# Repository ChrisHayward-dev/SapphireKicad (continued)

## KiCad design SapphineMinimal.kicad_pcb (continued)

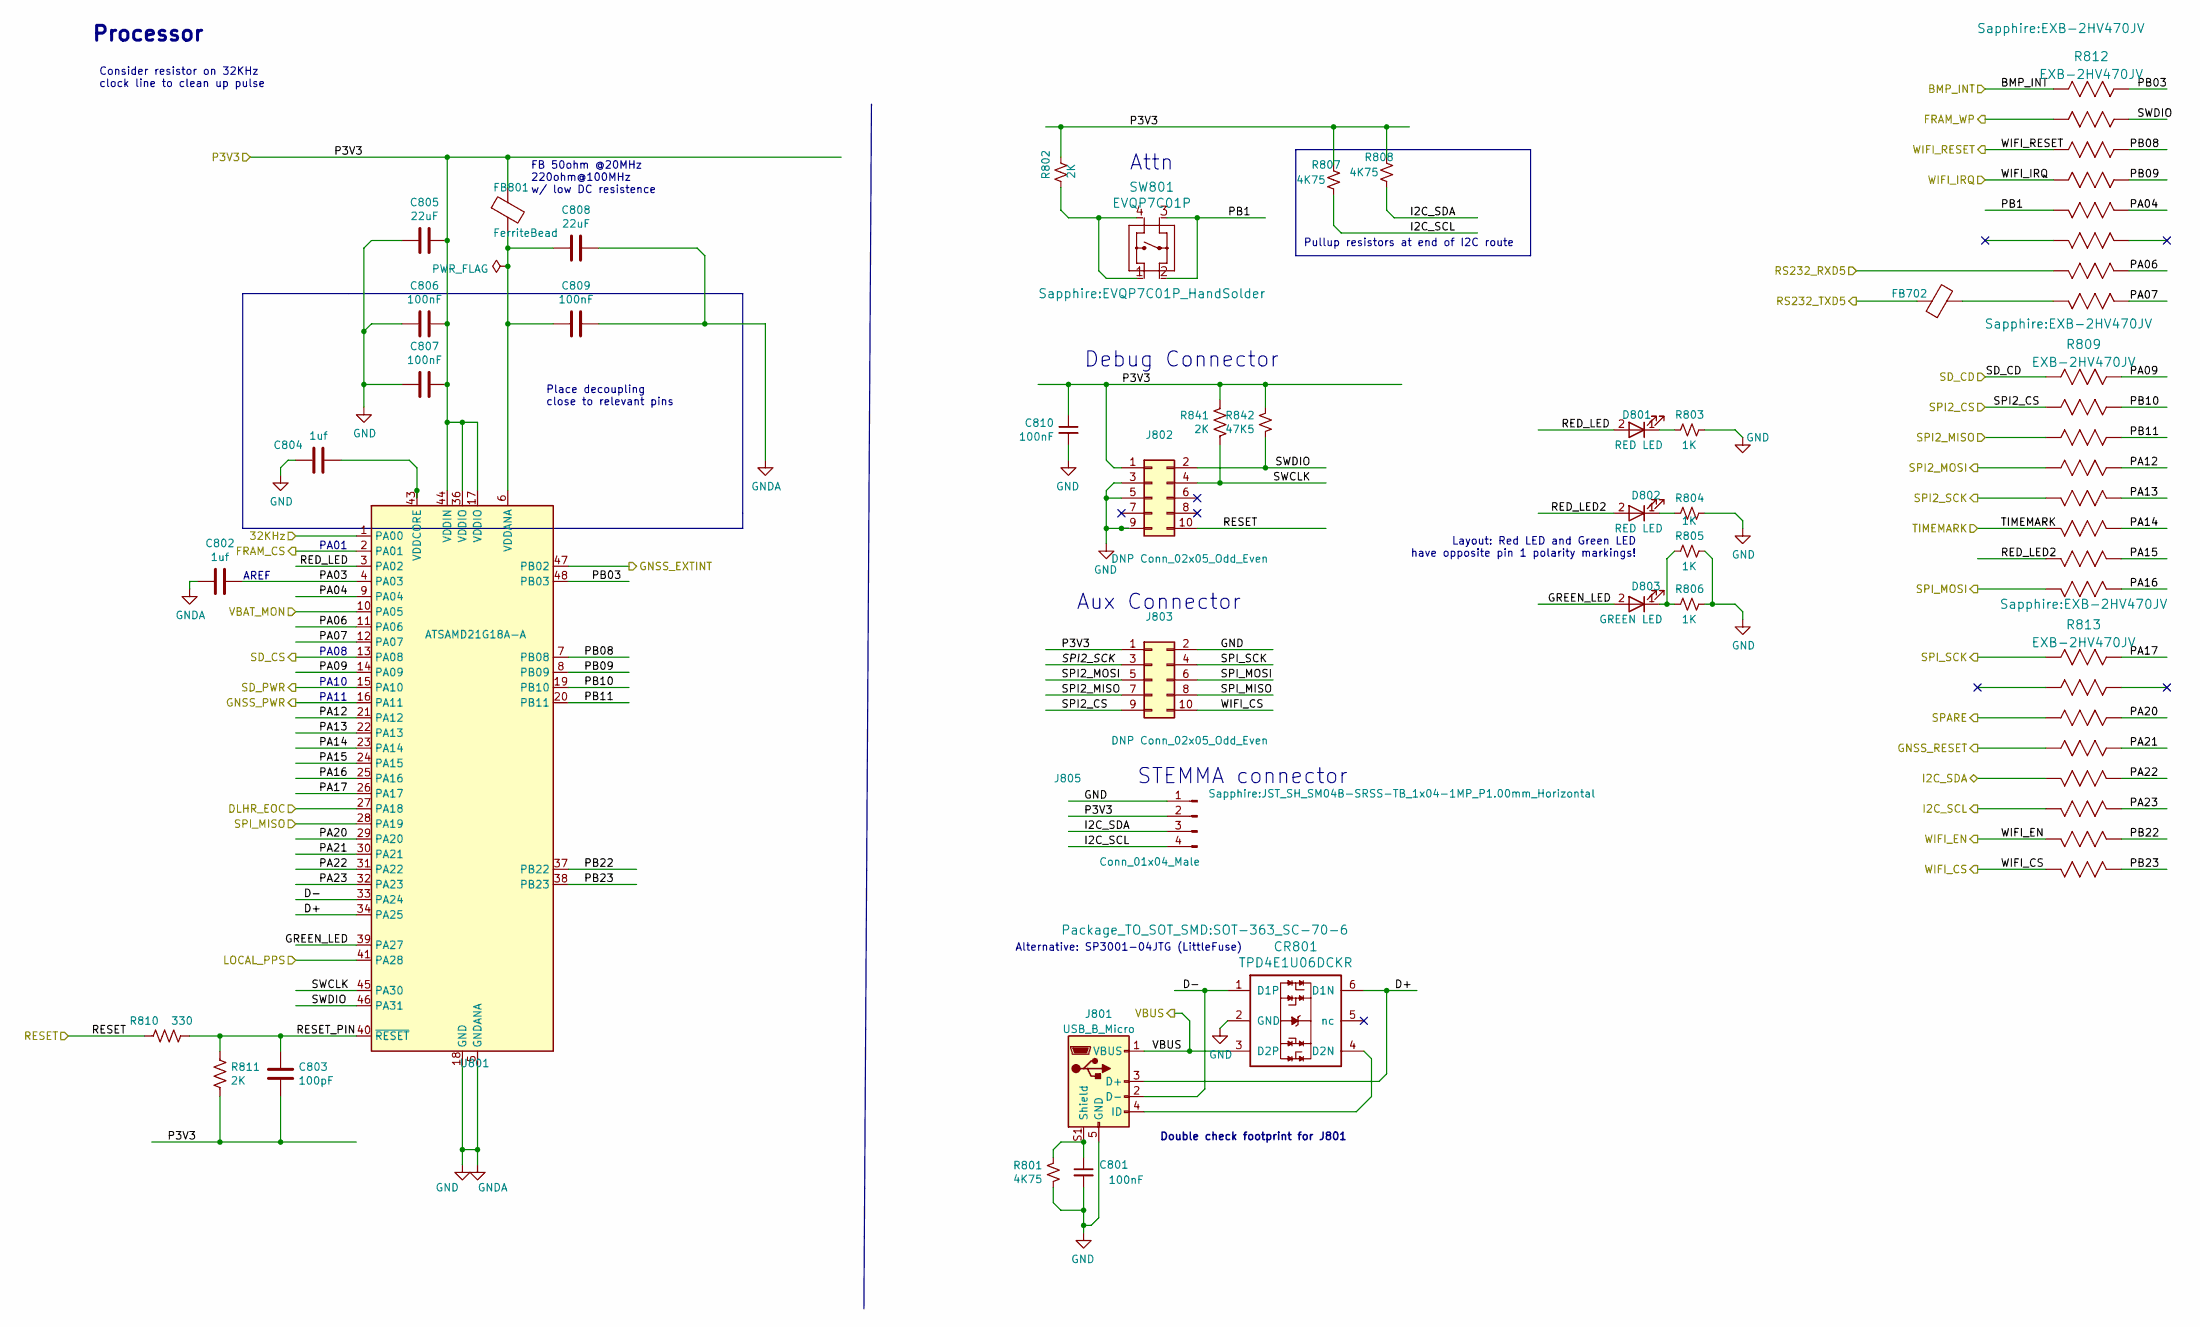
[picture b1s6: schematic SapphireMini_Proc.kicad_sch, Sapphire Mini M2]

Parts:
C801, C810: 100nF; C_0402_1005Metric; Tolerance 10%; Voltage 25; MPN CL05A104KA5NNNC; DigiKey Price 0.10
C802, C804: 1uf; C_0603_1608Metric; Voltage 16; MPN CL21B105KOFNNNG
C803: 100pF; C_0603_1608Metric; MPN 06035A101JAT2A
C805, C808: 22uF; C_0805_2012Metric; Voltage 16; MPN CL21A226MAYNNNE
C806, C807, C809: 100nF; C_0402_1005Metric; Voltage 25; MPN CL05A104KA5NNNC
CR801: TPD4E1U06DCKR; SOT-363_SC-70-6; MPN SP3001-04JTG; Digi-Key_PN F2915CT-ND
D801, D802: RED LED; LED_0805_2012Metric; MPN LTST-S220KRKT; DigiKey Price 0.28
D803: GREEN LED; LED_0805_2012Metric; MPN LTST-S220KGKT; DigiKey Price 0.28
FB702, FB801: FerriteBead; L_0603_1608Metric; MPN BLM18AG221SN1D
J801: USB_B_Micro; FCI_10118193-0001LF; MPN 10118193-0001LF
J802, J803: DNP Conn_02x05_Odd_Even; 3220-10-0100-00; MPN 3220-10-0100-00; DigiKey Price 0.58
J805: Conn_01x04_Male; JST_SH_SM04B-SRSS-TB_1x04-1MP_P1.00mm_Horizontal; MPN SM04B-SRSS-TB(LF)(SN); Digi-Key_PN 455-1804-1-ND
R801, R807, R808: 4K75; R_0603_1608Metric; Tolerance 5%; MPN CRCW06034K75FKEAC; DigiKey Price 0.05
R802: 2K; R_0603_1608Metric; Tolerance 5%; MPN CRCW06032K00FKEAC; DigiKey Price 0.05
R803, R804, R805, R806: 1K; R_0603_1608Metric; Tolerance 5%; MPN CRCW06031K00FKEAC; DigiKey Price 0.05
R809, R812, R813: EXB-2HV470JV; MPN EXB-2HV470JV
R810: 330; R_0603_1608Metric; MPN RC0603JR-07330RL
R811, R841: 2K; R_0603_1608Metric; MPN CRCW06032K00FKEAC
R842: 47K5; R_0603_1608Metric; Tolerance 1%; MPN CRCW060347K5FKEAC; DigiKey Price 0.10
SW801: EVQP7C01P; EVQP7C01P_HandSolder; MPN EVQ-P7C01P; Digi-Key_PN P16765CT-ND
U801: ATSAMD21G18A-A; TQFP-48_7x7mm_P0.5mm; MPN ATSAMD21G18A-AUT

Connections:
/DS3231/32KHz: U801.1 (PA00); also elsewhere on the board
/DS3231/SQW: U801.41 (PA28); also elsewhere on the board
/I2C_SCL: J805.4, R807.2, R813.6; also elsewhere on the board
/I2C_SDA: J805.3, R808.2, R813.5; also elsewhere on the board
/P3V3: C803.1, C805.1, C806.1, C807.1, C810.1, FB801.1, J802.1, J803.1, J805.2, R802.1, R807.1, R808.1, R811.2, R841.1, R842.2, U801.17 (VDDIO), U801.36 (VDDIO), U801.44 (VDDIN); also elsewhere on the board
/SPARE: R813.3; also elsewhere on the board
/SPI2_MISO: J803.7, R809.3; also elsewhere on the board
/SPI2_MOSI: J803.5, R809.4; also elsewhere on the board
/SPI2_SCK: J803.3, R809.5; also elsewhere on the board
/SapphireMini_DLHR/BMP_INT: R812.1; also elsewhere on the board
/SapphireMini_DLHR/DLHR_EOC: U801.27 (PA18); also elsewhere on the board
/SapphireMini_GNSS/GNSS_EXTINT: U801.47 (PB02); also elsewhere on the board
/SapphireMini_GNSS/GNSS_RESET: R813.4; also elsewhere on the board
/SapphireMini_GNSS/RS232_RXD: FB702.1; also elsewhere on the board
/SapphireMini_GNSS/RS232_TXD: R812.7; also elsewhere on the board
/SapphireMini_Power/GNSS_PWR: U801.16 (PA11); also elsewhere on the board
/SapphireMini_Power/SD_PWR: U801.15 (PA10); also elsewhere on the board
/SapphireMini_Power/VBAT_MON: U801.10 (PA05); also elsewhere on the board
/SapphireMini_Power/VBUS: CR801.3 (D2P), J801.1 (VBUS); also elsewhere on the board
/SapphireMini_SD/FRAM_CS: U801.2 (PA01); also elsewhere on the board
/SapphireMini_SD/FRAM_WP: R812.2; also elsewhere on the board
/SapphireMini_SD/SD_CS: U801.13 (PA08); also elsewhere on the board
/SapphireMini_SD/SPI_MISO: J803.8, U801.28 (PA19); also elsewhere on the board
/SapphireMini_SD/SPI_MOSI: J803.6, R809.8; also elsewhere on the board
/SapphireMini_SD/SPI_SCK: J803.4, R813.1; also elsewhere on the board
/Sapphire_Proc/D+: CR801.6 (D1N), J801.3 (D+), U801.34 (PA25)
/Sapphire_Proc/D-: CR801.1 (D1P), J801.2 (D-), U801.33 (PA24)
/Sapphire_Proc/GREEN_LED: D803.2 (A), U801.39 (PA27)
/Sapphire_Proc/PA03: C802.1, U801.4 (PA03)
/Sapphire_Proc/PA04: R812.12, U801.9 (PA04)
/Sapphire_Proc/PA06: R812.10, U801.11 (PA06)
/Sapphire_Proc/PA07: R812.9, U801.12 (PA07)
/Sapphire_Proc/PA09: R809.16, U801.14 (PA09)
/Sapphire_Proc/PA12: R809.13, U801.21 (PA12)
/Sapphire_Proc/PA13: R809.12, U801.22 (PA13)
/Sapphire_Proc/PA14: R809.11, U801.23 (PA14)
/Sapphire_Proc/PA15: R809.10, U801.24 (PA15)
/Sapphire_Proc/PA16: R809.9, U801.25 (PA16)
/Sapphire_Proc/PA17: R813.16, U801.26 (PA17)
/Sapphire_Proc/PA20: R813.14, U801.29 (PA20)
/Sapphire_Proc/PA21: R813.13, U801.30 (PA21)
/Sapphire_Proc/PA22: R813.12, U801.31 (PA22)
/Sapphire_Proc/PA23: R813.11, U801.32 (PA23)
/Sapphire_Proc/PB1: R812.5, SW801.2, SW801.3
/Sapphire_Proc/PB03: R812.16, U801.48 (PB03)
/Sapphire_Proc/PB08: R812.14, U801.7 (PB08)
/Sapphire_Proc/PB09: R812.13, U801.8 (PB09)
/Sapphire_Proc/PB10: R809.15, U801.19 (PB10)
/Sapphire_Proc/PB11: R809.14, U801.20 (PB11)
/Sapphire_Proc/PB22: R813.10, U801.37 (PB22)
/Sapphire_Proc/PB23: R813.9, U801.38 (PB23)
/Sapphire_Proc/RED_LED: D801.2 (A), U801.3 (PA02)
/Sapphire_Proc/RED_LED2: D802.2 (A), R809.7
/Sapphire_Proc/RESET: J802.10, R810.2; also elsewhere on the board
/Sapphire_Proc/RESET_PIN: C803.2, R810.1, R811.1, U801.40 (~RESET)
/Sapphire_Proc/SD_CD: R809.1; also elsewhere on the board
/Sapphire_Proc/SPI2_CS: J803.9, R809.2
/Sapphire_Proc/SWCLK: J802.4, R841.2, U801.45 (PA30)
/Sapphire_Proc/SWDIO: J802.2, R812.15, R842.1, U801.46 (PA31)
/Sapphire_Proc/TIMEMARK: R809.6; also elsewhere on the board
/Sapphire_Proc/WIFI_CS: J803.10, R813.8; also elsewhere on the board
/Sapphire_Proc/WIFI_EN: R813.7; also elsewhere on the board
/WIFI_IRQ: R812.4; also elsewhere on the board
/WIFI_RST: R812.3; also elsewhere on the board
GND: C801.2, C802.2, C804.2, C805.2, C806.2, C807.2, C808.1, C809.1, C810.2, CR801.2 (GND), J801.5 (GND), J802.3, J802.5, J802.9, J803.2, J805.1, R801.1, R803.2, R804.2, R805.2, R806.2, U801.5 (GNDANA), U801.18 (GND), U801.35 (GND), U801.42 (GND); also elsewhere on the board
unnamed: C801.1, J801.S1 (Shield), R801.2
unnamed: C804.1, U801.43 (VDDCORE)
unnamed: C808.2, C809.2, FB801.2, U801.6 (VDDANA)
unnamed: CR801.4 (D2N), J801.4 (ID)
unnamed: D801.1 (K), R803.1
unnamed: D802.1 (K), R804.1
unnamed: D803.1 (K), R805.1, R806.1
unnamed: FB702.2, R812.8
unnamed: R802.2, SW801.1, SW801.4

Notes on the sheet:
PA08
PA10
PA11
Double check footprint for J801
Processor
Layout: Red LED and Green LED have opposite pin 1 polarity markings!
Debug Connector
AREF
Attn
Alternative: SP3001-04JTG (LittleFuse)
PA01
Pullup resistors at end of I2C route
FB 50ohm @20MHz 220ohm@100MHz w/ low DC resistence
STEMMA connector
Consider resistor on 32KHz clock line to clean up pulse
Place decoupling close to relevant pins
Aux Connector

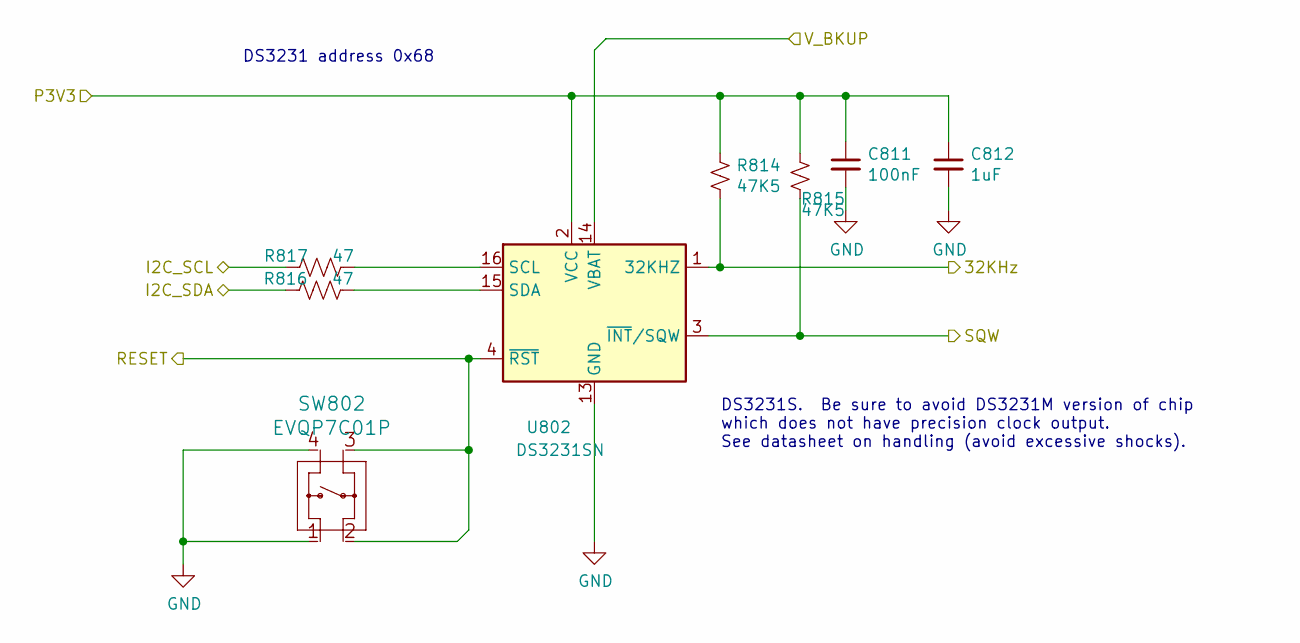
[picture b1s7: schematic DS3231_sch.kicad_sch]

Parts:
C811: 100nF; C_0402_1005Metric; Tolerance 10%; Voltage 25; MPN CL05A104KA5NNNC; DigiKey Price 0.10
C812: 1uF; C_0805_2012Metric; Tolerance 10%; Voltage 16; MPN CL21B105KOFNNNG; DigiKey Price 0.06
R814, R815: 47K5; R_0603_1608Metric; Tolerance 1%; MPN CRCW060347K5FKEAC; DigiKey Price 0.10
R816, R817: 47; R_0603_1608Metric; MPN CRCW060347R0FKEAC
SW802: EVQP7C01P; EVQP7C01P_HandSolder; MPN EVQ-P7C01P; Digi-Key_PN P16765CT-ND
U802: DS3231SN; SOIC-16W_7.5x10.3mm_P1.27mm; MPN DS3231SN#T&R; Digi-Key_PN DS3231SN#T&RCT-ND

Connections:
/DS3231/32KHz: R814.2, U802.1 (32KHZ); also elsewhere on the board
/DS3231/SQW: R815.2, U802.3 (~INT/SQW); also elsewhere on the board
/I2C_SCL: R817.2; also elsewhere on the board
/I2C_SDA: R816.2; also elsewhere on the board
/P3V3: C811.1, C812.1, R814.1, R815.1, U802.2 (VCC); also elsewhere on the board
/Sapphire_Proc/RESET: SW802.2, SW802.3, U802.4 (~RST); also elsewhere on the board
/V_BKUP: U802.14 (VBAT); also elsewhere on the board
GND: C811.2, C812.2, SW802.1, SW802.4, U802.5 (GND), U802.6 (GND), U802.7 (GND), U802.8 (GND), U802.9 (GND), U802.10 (GND), U802.11 (GND), U802.12 (GND), U802.13 (GND); also elsewhere on the board
unnamed: R816.1, U802.15 (SDA)
unnamed: R817.1, U802.16 (SCL)

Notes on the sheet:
DS3231 address 0x68
DS3231S. Be sure to avoid DS3231M version of chip which does not have precision clock output. See datasheet on handling (avoid excessive shocks).

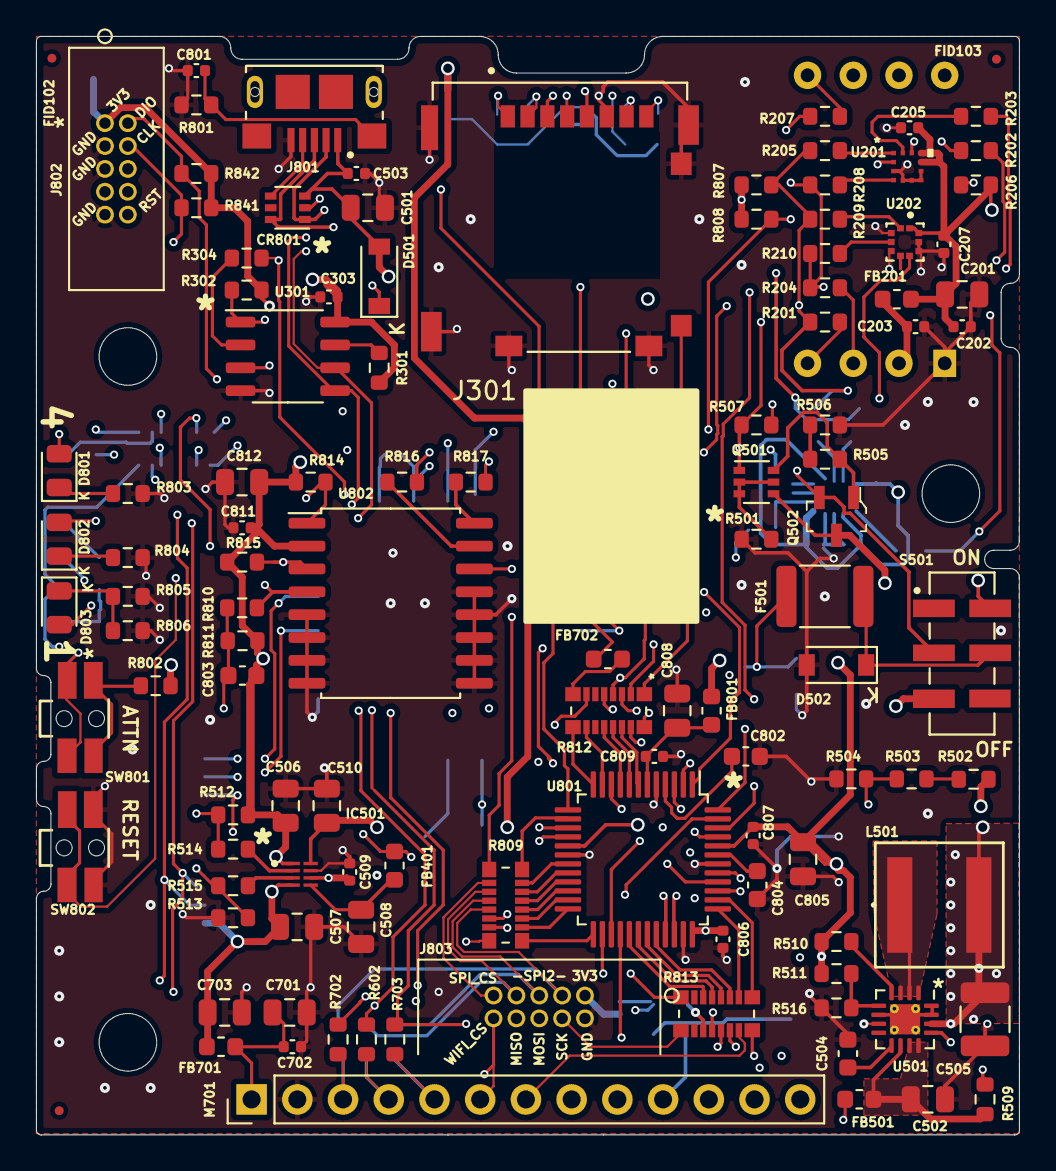
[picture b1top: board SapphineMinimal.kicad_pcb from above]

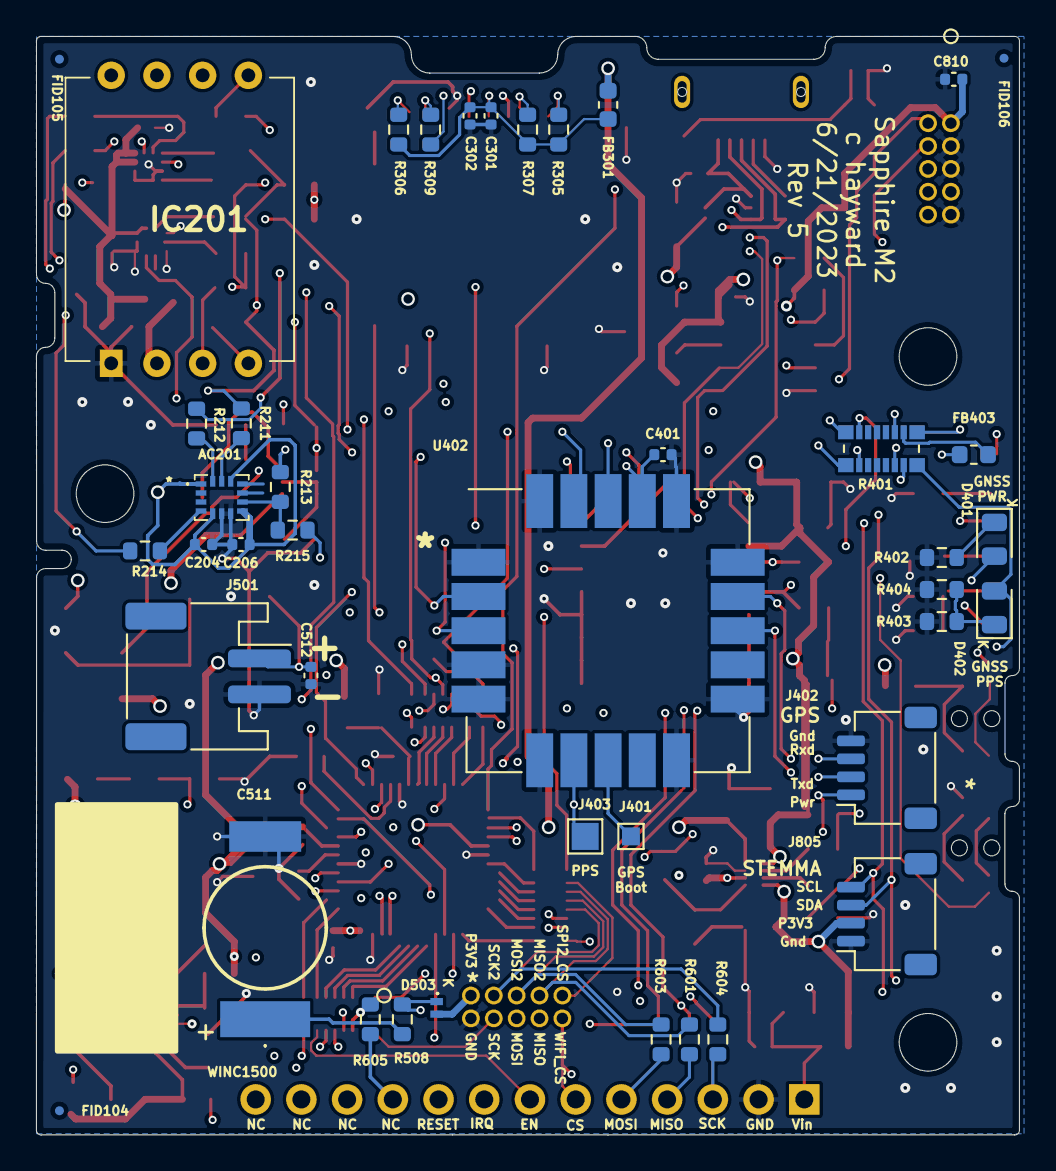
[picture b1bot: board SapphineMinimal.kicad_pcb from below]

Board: 4 copper layers, 54.6 x 61.0 mm, 159 parts (42 on the bottom side), 133 nets.

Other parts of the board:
C701, C703: 22uF; C_0805_2012Metric
C702: 100nF; C_0402_1005Metric
FB701: FerriteBead; L_0603_1608Metric
M701: DNP AdafruitWINC1500; PinHeader_1x13_P2.54mm_Vertical
R601: 0; R_0603_1608Metric
R602: DNP 0; R_0603_1608Metric
R603, R604: 47; R_0603_1608Metric
R605, R702, R703: DNP 47; R_0603_1608Metric

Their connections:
/P3V3: C703.1, FB701.1; also elsewhere on the board
/SPARE: R605.2; also elsewhere on the board
/SPI2_MISO: R601.1; also elsewhere on the board
/SPI2_MOSI: R603.2; also elsewhere on the board
/SPI2_SCK: R604.2; also elsewhere on the board
/SapphireMini_SD/SPI_MISO: R602.1; also elsewhere on the board
/SapphireMini_SD/SPI_MOSI: R703.2; also elsewhere on the board
/SapphireMini_SD/SPI_SCK: R702.2; also elsewhere on the board
/Sapphire_Proc/WIFI_CS: M701.6 (CS); also elsewhere on the board
/Sapphire_Proc/WIFI_EN: M701.7 (EN); also elsewhere on the board
/Sapphire_WiFi/WSPI_MISO: M701.4 (MISO), R601.2, R602.2
/Sapphire_WiFi/WSPI_MOSI: M701.5 (MOSI), R603.1, R703.1
/Sapphire_WiFi/WSPI_SCK: M701.3 (SCK), R604.1, R702.1
/WIFI_IRQ: M701.8 (IRQ); also elsewhere on the board
/WIFI_RST: M701.9 (RST); also elsewhere on the board
GND: C701.2, C702.2, C703.2, M701.2 (Gnd); also elsewhere on the board
unnamed: C701.1, C702.1, FB701.2, M701.1 (Vin)
unnamed: M701.10 (WAKE), R605.1

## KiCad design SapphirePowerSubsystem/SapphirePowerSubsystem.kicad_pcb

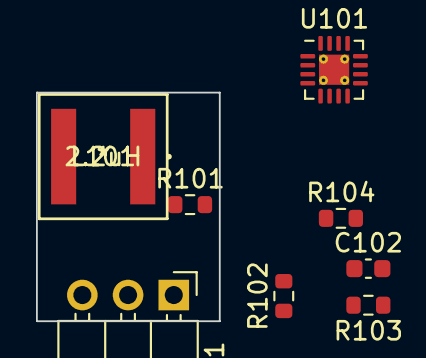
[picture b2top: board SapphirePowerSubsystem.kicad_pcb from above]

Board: 2 copper layers, 10.2 x 12.7 mm, 8 parts (0 on the bottom side), 8 nets, no tracks yet.

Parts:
C102: 390pF; C_0603_1608Metric
J101: Conn_01x03_Male; PinHeader_1x03_P2.54mm_Horizontal
L101: 2.2uH; 74439344022
R101, R102: 100K; R_0603_1608Metric
R103: 562K; R_0603_1608Metric
R104: 180K; R_0603_1608Metric
U101: TPS62150; VQFN-16-1EP_3x3mm_P0.5mm_EP1.68x1.68mm_ThermalVias

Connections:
/P3V3: J101.3, L101.1, R102.1, R103.1, U101.7 (FSW), U101.14 (VOS)
/VBAT_EN: R101.2, U101.13 (EN)
/Vin: J101.1, R101.1, U101.10 (AVIN), U101.11 (PVIN), U101.12 (PVIN)
GND: C102.2, J101.2, R104.2, U101.6 (AGND), U101.15 (PGND), U101.16 (PGND), U101.17 (EP)
unnamed: C102.1, U101.9 (SS/TR)
unnamed: L101.2, U101.1 (SW), U101.2 (SW), U101.3 (SW)
unnamed: R102.2, U101.4 (PG)
unnamed: R103.2, R104.1, U101.5 (FB)

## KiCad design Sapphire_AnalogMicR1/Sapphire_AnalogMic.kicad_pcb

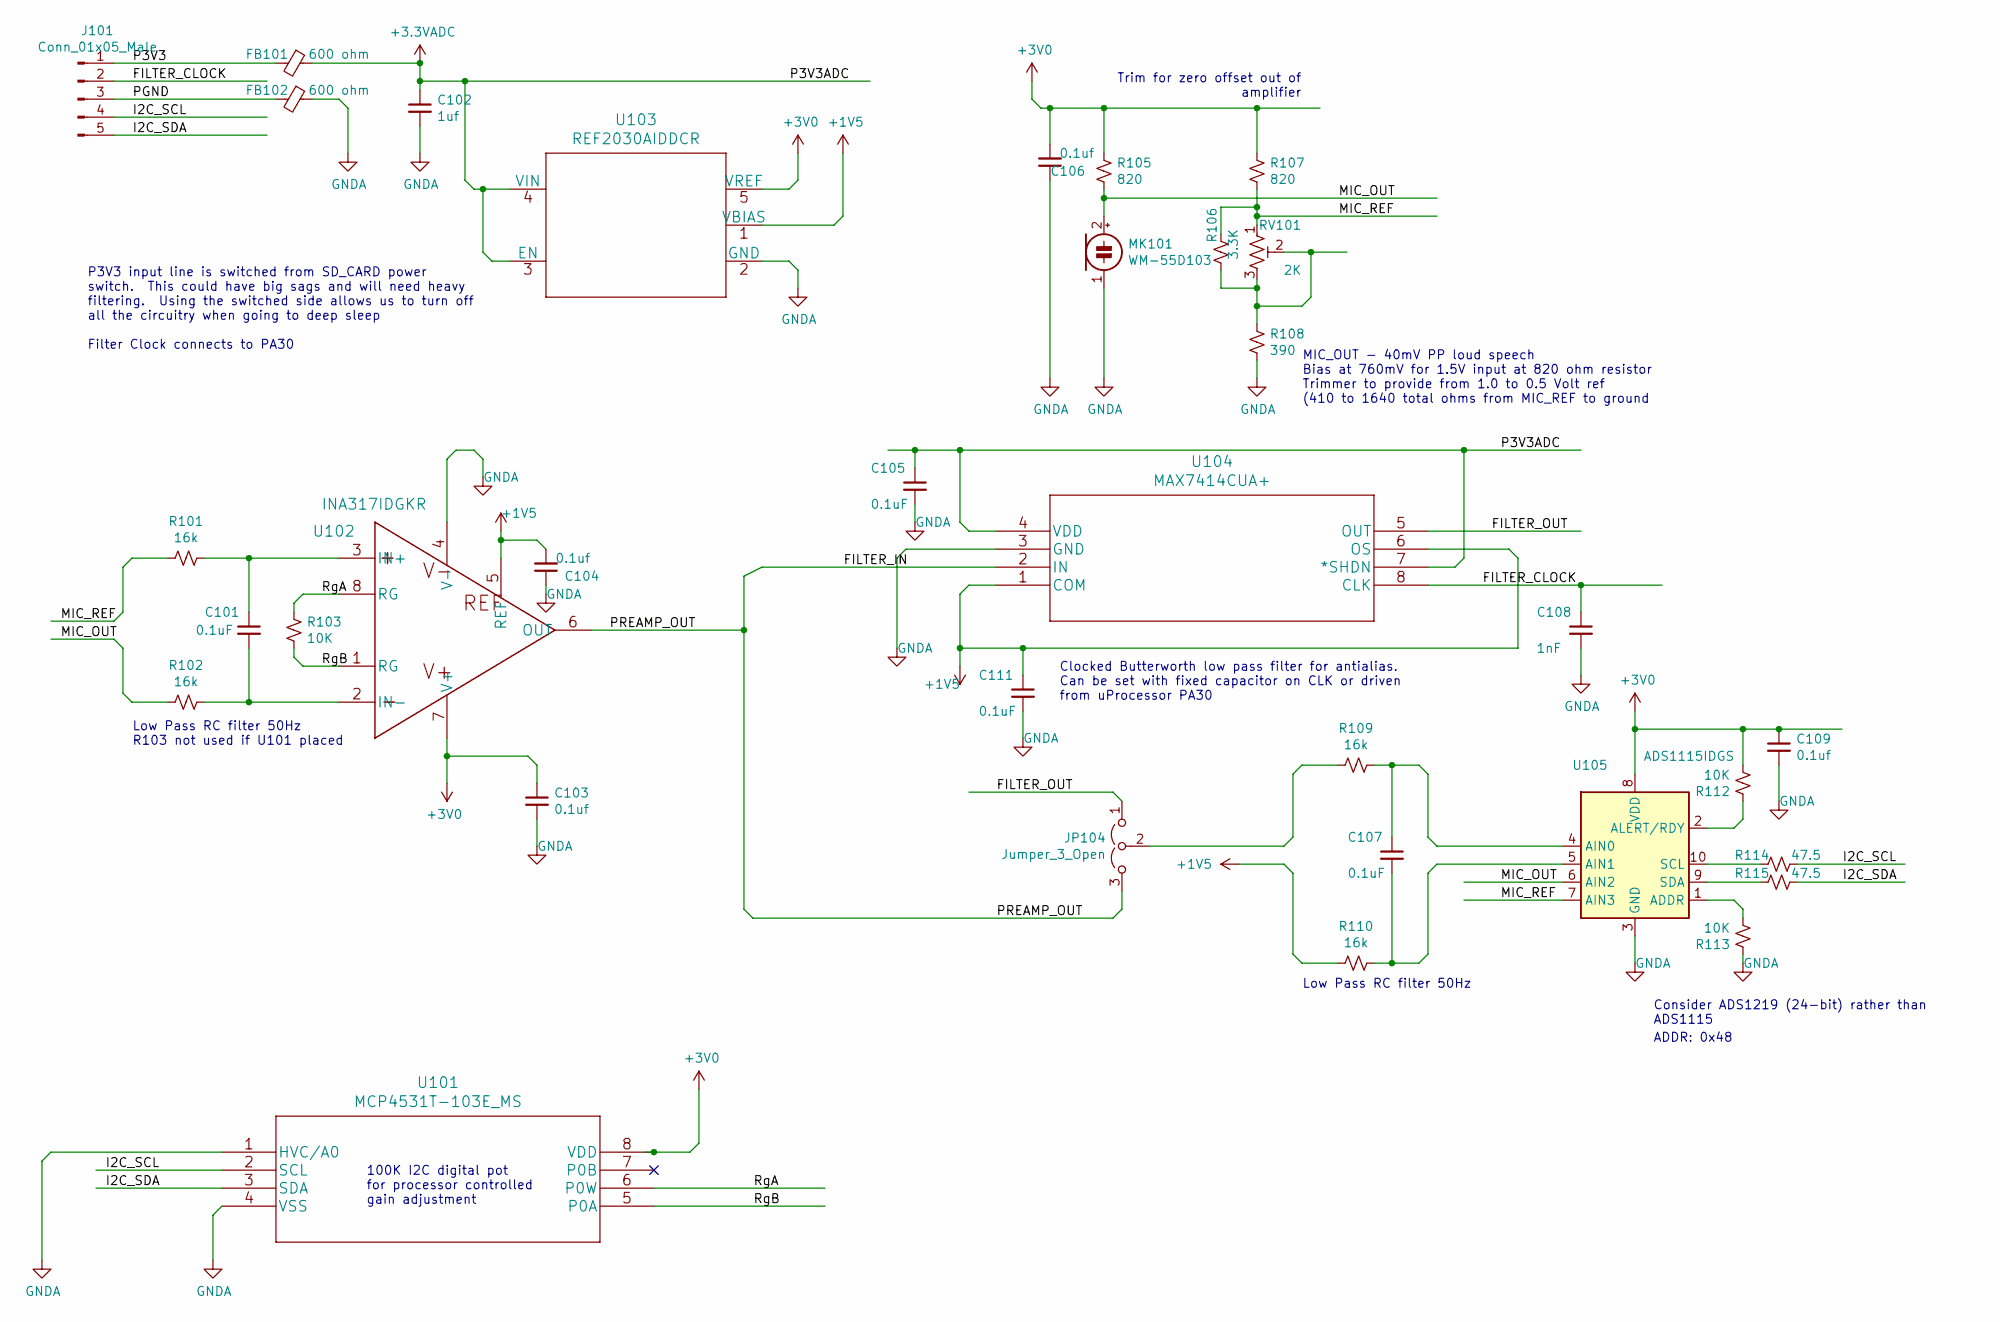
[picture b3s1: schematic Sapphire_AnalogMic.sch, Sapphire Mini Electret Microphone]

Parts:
C101, C105, C107, C111: 0.1uF; C_0603_1608Metric
C102: 1uf; C_0603_1608Metric
C103, C104, C106, C109: 0.1uf; C_0603_1608Metric
C108: 1nF; C_0603_1608Metric
FB101, FB102: 600 ohm; R_0603_1608Metric
J101: Conn_01x05_Male; PinHeader_1x05_P2.54mm_Vertical
JP104: Jumper_3_Open; SolderJumper-3_P1.3mm_Open_RoundedPad1.0x1.5mm_NumberLabels
MK101: WM-55D103; PinHeader_1x02_P2.54mm_Vertical
R101, R102, R109, R110: 16k; R_0603_1608Metric
R103, R112, R113: 10K; R_0603_1608Metric
R105, R107: 820; R_0603_1608Metric
R106: 3.3K; R_0603_1608Metric
R108: 390; R_0603_1608Metric
R114, R115: 47.5; R_0603_1608Metric
RV101: 2K; Potentiometer_Bourns_3296W_Vertical
U101: MCP4531T-103E_MS; MAX7414CUA&plus_
U102: INA317IDGKR
U103: REF2030AIDDCR
U104: MAX7414CUA+; MAX7414CUA&plus_
U105: ADS1115IDGS; TSSOP-10_3x3mm_P0.5mm

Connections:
+1V5: C104.2, C111.1, R110.2, U102.5 (REF), U103.1 (VBIAS), U104.1 (COM), U104.6 (OS)
+3.3VADC: C102.1, C105.1, FB101.1, U103.3 (EN), U103.4 (VIN), U104.4 (VDD), U104.7 (*SHDN)
+3V0: C103.1, C106.2, C109.1, R105.1, R107.1, R112.2, U101.8 (VDD), U102.7 (V+), U103.5 (VREF), U105.8 (VDD)
/FILTER_CLOCK: C108.1, J101.2, U104.8 (CLK)
/FILTER_IN: JP104.3 (B), U102.6 (OUT), U104.2 (IN)
/FILTER_OUT: JP104.1 (A), U104.5 (OUT)
/I2C_SCL: J101.4, R114.1, U101.2 (SCL)
/I2C_SDA: J101.5, R115.1, U101.3 (SDA)
/MIC_OUT: MK101.2 (+), R102.2, R105.2, U105.6 (AIN2)
/MIC_REF: R101.2, R106.1, R107.2, RV101.1, U105.7 (AIN3)
/P3V3: FB101.2, J101.1
/PGND: FB102.2, J101.3
/RgA: R103.1, U101.6 (P0W), U102.8 (RG)
/RgB: R103.2, U101.5 (P0A), U102.1 (RG)
GNDA: C102.2, C103.2, C104.1, C105.2, C106.1, C108.2, C109.2, C111.2, FB102.1, MK101.1 (-), R108.2, R113.1, U101.1 (HVC/A0), U101.4 (VSS), U102.4 (V-), U103.2 (GND), U104.3 (GND), U105.3 (GND)
unnamed: C101.1, R101.1, U102.3 (IN+)
unnamed: C101.2, R102.1, U102.2 (IN-)
unnamed: C107.1, R109.1, U105.4 (AIN0)
unnamed: C107.2, R110.1, U105.5 (AIN1)
unnamed: JP104.2 (C), R109.2
unnamed: R106.2, R108.1, RV101.2, RV101.3
unnamed: R112.1, U105.2 (ALERT/RDY)
unnamed: R113.2, U105.1 (ADDR)
unnamed: R114.2, U105.10 (SCL)
unnamed: R115.2, U105.9 (SDA)

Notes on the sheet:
100K I2C digital pot for processor controlled gain adjustment
Low Pass RC filter 50Hz
Low Pass RC filter 50Hz R103 not used if U101 placed
Trim for zero offset out of amplifier
MIC_OUT - 40mV PP loud speech Bias at 760mV for 1.5V input at 820 ohm resistor Trimmer to provide from 1.0 to 0.5 Volt ref (410 to 1640 total ohms from MIC_REF to ground
Consider ADS1219 (24-bit) rather than ADS1115
P3V3 input line is switched from SD_CARD power switch. This could have big sags and will need heavy filtering. Using the switched side allows us to turn off all the circuitry when going to deep sleep Filter Clock connects to PA30
Clocked Butterworth low pass filter for antialias. Can be set with fixed capacitor on CLK or driven from uProcessor PA30
ADDR: 0x48

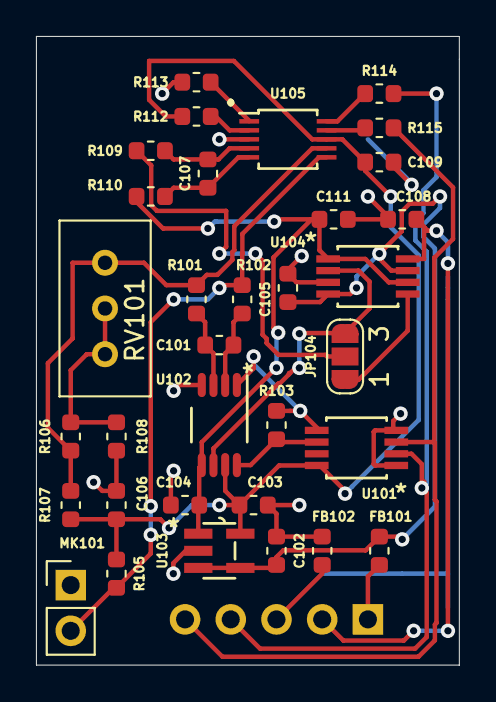
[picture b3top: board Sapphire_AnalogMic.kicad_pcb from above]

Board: 2 copper layers, 23.5 x 34.9 mm, 34 parts (1 on the bottom side), 25 nets.
